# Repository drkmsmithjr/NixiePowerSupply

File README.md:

# [Nixie Tube Power Supply](https://wp.me/p85ddV-B1 )

See [www.surfncircuits.com](https://wp.me/p85ddV-B1)  for a complete description.  This github repository contains the Kicad Schematic, Spice Simulation, Efficiency Calculations of the 5v to 170v DCM Boost Converter for Powering your Nixie Tubes.   

__KC_NixieSupply5vto160v__:  Kicad schematic, PCB layout, BOM.  The footprint is 1.5" x 1.5" and was described and optimized in Part 2 of the blog.     The Board can be ordered from __oshpark.com__.<a href="https://oshpark.com/shared_projects/FZ5eYIVY"></img></a>

__KC_NixieSupply5vto170vMini__:  KiCad schematic, PCB Layout, BOM of the "mini" version of the supply.   This has a footprint of 1.5" x 1" by using smaller output capacitors and using the KiCad power tools to shrink the layout.  This is the system defined by part 3 of the blog.    The layout has all the same constraints as in Part 2.  It still has four mounting holes, a USB input connector and a Terminal output connector.    You can order the board from __oshpark.com__. <a href="https://oshpark.com/shared_projects/UnjheFwg"></img></a>

__SimCalcFiles__:  Spice simulation files and DCM Efficiency Calculations.  NOTE: The LTSPICE (TM) simulation has trouble finding an initial operating point.   To get the simulation to start, use the ESC key and press it twice to skip the initial operating point.   This allows the simulation to continue and will provide a good transient response.    

__Datasheeets__: Datasheets for different inductors and the power fet.  In the Kicad Schematic, the part numbers and Digikey (TM) links are listed already.   Also the complete BOM is located in the KICAD Directory.      

See the complete blogs entry at  www.surfncircuits.com
  * [Designing a Small Footprint, Low Profile 5v to 170v Nixie Tube Power Supply (Part 1)](https://wp.me/p85ddV-A8 )
  * [Optimizing the design of the 5v to 170v Nixie Tube Power Supply (Part 2)](https://wp.me/p85ddV-B1 )
  * [KiCad Power Tools Help Shrink The Nixie Tube Power Supply (part 3)](https://wp.me/p85ddV-Ck)

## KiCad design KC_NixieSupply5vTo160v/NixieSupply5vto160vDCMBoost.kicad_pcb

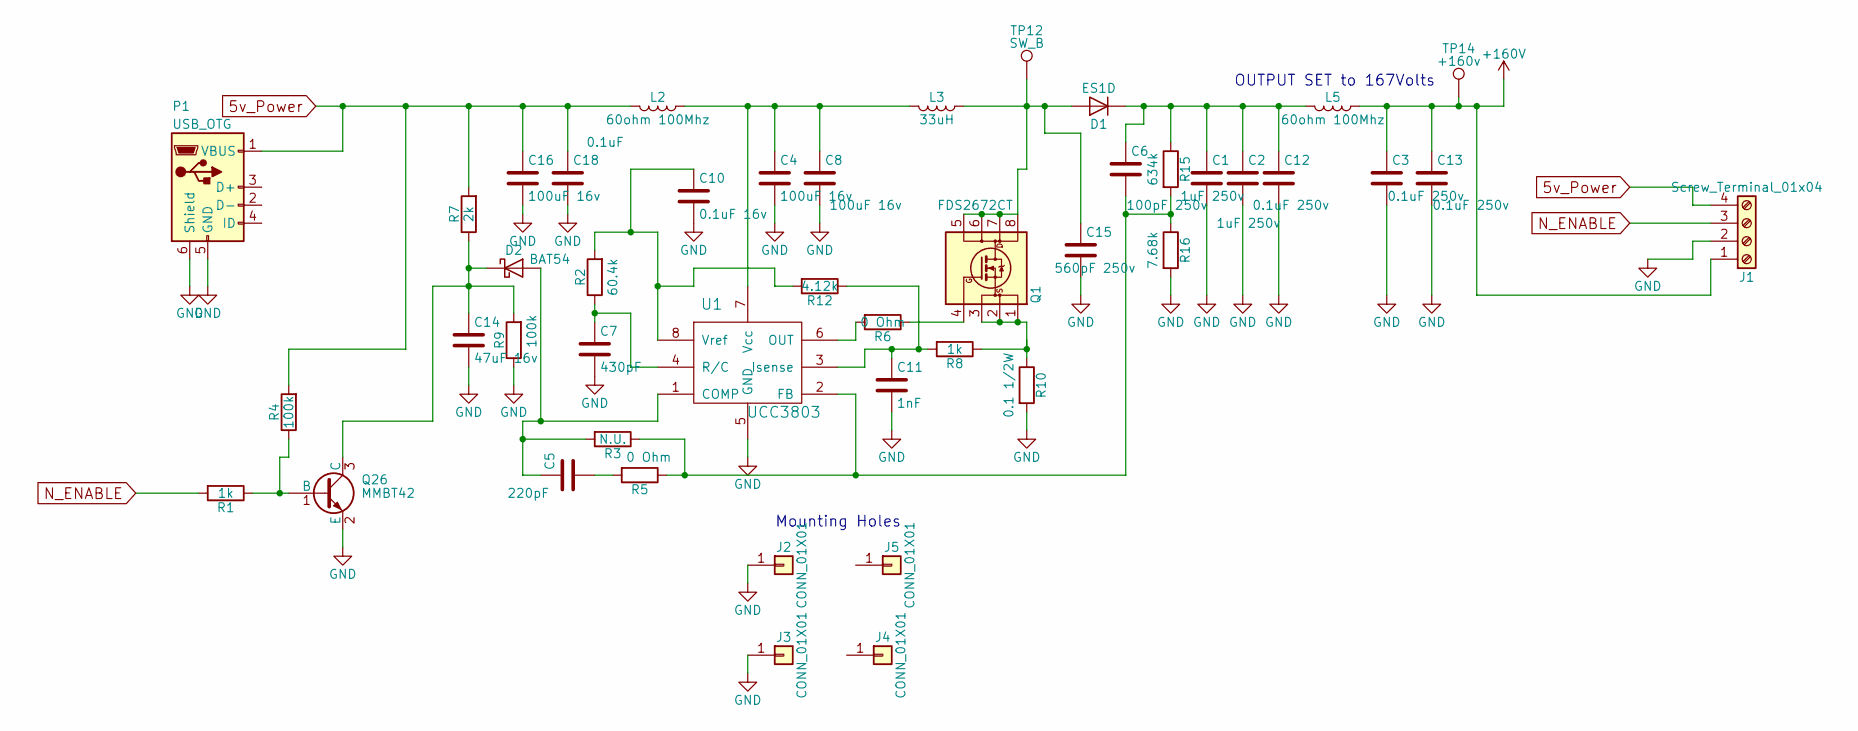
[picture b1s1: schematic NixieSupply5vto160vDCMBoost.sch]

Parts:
C1, C2: 1uF 250v; C_2220_HandSoldering; MPN GRM55DR72E105KW01L
C3, C12, C13: 0.1uF 250v; C_0805; MPN CGA4J3X7T2E104M125AE
C4, C8, C16: 100uF 16v; C_1210; MPN EMK325ABJ107MM-P
C5: 220pF; C_0805
C6: 100pF 250v; C_0805; MPN CC0805C101JAGAC7800
C7: 430pF; C_0805; MPN CL21C431JBANNNC
C10: 0.1uF 16v; C_0805
C11: 1nF; C_0805
C14: 47uF 16v; C_1206; MPN C3216JB1C476M160AB
C15: 560pF 250v; C_0603; MPN C0603C561JAGAC7867
C18: 0.1uF; C_0805
D1: ES1D; D_SMA_Handsoldering; MPN ES1D
D2: BAT54; D_SOD-323_HandSoldering; MPN BAT54WS-7-F
J1: Screw_Terminal_01x04; TerminalBlock_Phoenix_PT-3.5mm_4pol; MPN 1984633
J2, J3: CONN_01X01; MountingHole_2.2mm_M2_Pad
J4, J5: CONN_01X01; MountingHole_2.2mm_M2
L2: 60ohm 100Mhz; R_0805; MPN BKP2125HS600-T
L3: 33uH; Choke_SMD_12x12mm_Wurth_WE-PD; MPN 7447709330
L5: 60ohm 100Mhz; R_0805
P1: USB_OTG; USB_Micro-B_Wurth_3A_Non-OVAL-Drill; MPN 629105150521
Q1: FDS2672CT; SOIC-8-N; MPN FDS2672CT-ND
Q26: MMBT42; SOT-23
R1, R8: 1k; R_0805
R2: 60.4k; R_0805
R3: N.U.; R_0805
R4, R9: 100k; R_0805
R5, R6: 0 Ohm; R_0805
R7: 2k; R_0805
R10: 0.1 1/2W; R_0805; MPN ERJ-6DSFR10V
R12: 4.12k; R_0805
R15: 634k; R_0805
R16: 7.68k; R_0805
TP12: SW_B; PINTST
TP14: +160v; PINTST
U1: UCC3803; SOIC-8-N; MPN UCC3803DTR

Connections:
5v_Power: C16.1, C18.1, J1.4, L2.2, P1.1 (VBUS), R4.2, R7.2
+160V: C3.1, C13.1, J1.1, L5.1, TP14.1
GND: C1.2, C2.2, C3.2, C4.2, C7.2, C8.2, C10.2, C11.2, C12.2, C13.2, C14.2, C15.2, C16.2, C18.2, J1.2, J2.1, J3.1, P1.5 (GND), P1.6 (Shield), Q26.2 (E), R9.1, R10.2, R16.2, U1.5 (GND)
N_ENABLE: J1.3, R1.2
unnamed: C1.1, C2.1, C6.1, C12.1, D1.1 (K), L5.2, R15.1
unnamed: C4.1, C8.1, L2.1, L3.2, U1.7 (Vcc)
unnamed: C5.1, D2.2 (A), R3.2, U1.1 (COMP)
unnamed: C5.2, R5.2
unnamed: C6.2, R3.1, R5.1, R15.2, R16.1, U1.2 (FB)
unnamed: C7.1, R2.1, U1.4 (R/C)
unnamed: C10.1, R2.2, R12.2, U1.8 (Vref)
unnamed: C11.1, R8.2, R12.1, U1.3 (Isense)
unnamed: C14.1, D2.1 (K), Q26.3 (C), R7.1, R9.2
unnamed: C15.1, D1.2 (A), L3.1, Q1.5 (D), Q1.6 (D), Q1.7 (D), Q1.8 (D), TP12.1
unnamed: P1.2 (D-), P1.3 (D+)
unnamed: Q1.1 (S), Q1.2 (S), Q1.3 (S), R8.1, R10.1
unnamed: Q1.4 (G), R6.1
unnamed: Q26.1 (B), R1.1, R4.1
unnamed: R6.2, U1.6 (OUT)

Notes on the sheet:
Mounting Holes
OUTPUT SET to 167Volts

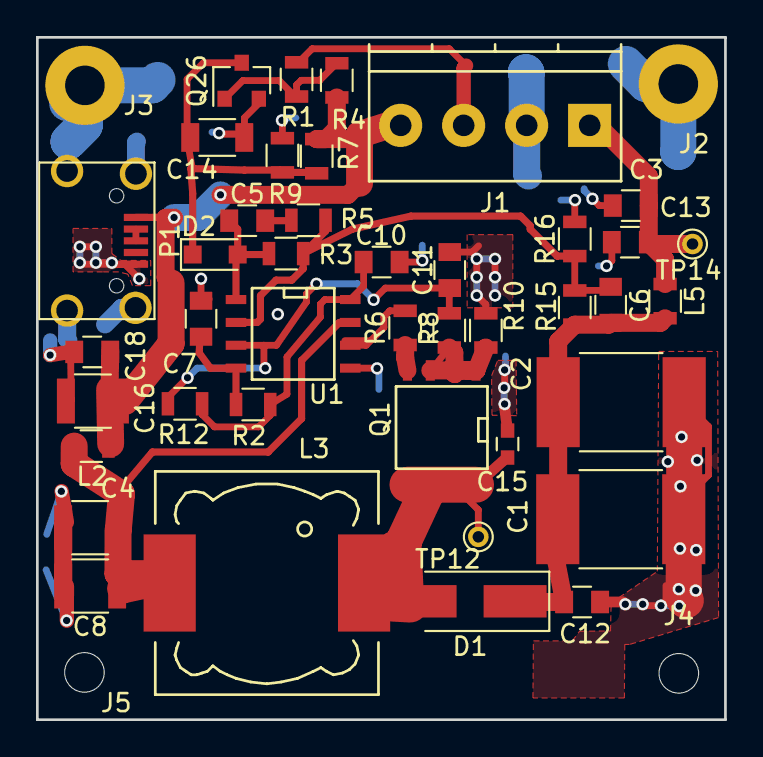
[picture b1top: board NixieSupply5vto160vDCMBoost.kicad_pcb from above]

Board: 2 copper layers, 38.2 x 37.9 mm, 45 parts (0 on the bottom side), 19 nets.

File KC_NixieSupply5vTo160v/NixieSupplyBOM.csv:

,,,,,,
Tool:,Eeschema 4.0.7,,,,,
Generator:,C:/Program Files/KiCad/bin/scripting/plugins/bom_csv_grouped_by_value.py,,,,,
,,,,,,
Item,Qty,Reference(s),Value,Footprint,Datasheet,MPN
1,2,"C1, C2",1uF 250v,Capacitors_SMD:C_2220_HandSoldering,https://www.digikey.com/product-detail/en/murata-electronics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,GRM55DR72E105KW01L
2,3,"C3, C12, C13",0.1uF 250v,Capacitors_SMD:C_0805,,
3,5,"C4, C8, C9, C14, C16",47uF 10v,Capacitors_SMD:C_0805,http://www.digikey.com/product-detail/en/murata-electronics-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,GRM21BR61A476ME15L
4,1,C5,220pF,Capacitors_SMD:C_0805,,
5,1,C6,100pF 250v,Capacitors_SMD:C_0805,,
6,1,C7,330pF,Capacitors_SMD:C_0805,,
7,1,C10,0.1uF 16v,Capacitors_SMD:C_0805,,
8,1,C11,1nF,Capacitors_SMD:C_0805,,
9,1,C15,47pF 250v,Capacitors_SMD:C_0603,http://www.digikey.com/product-detail/en/tdk-corporation/C16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,C1608C0G2E331J080AA
10,1,C18,0.1uF,Capacitors_SMD:C_0805,,
11,1,D1,DFLS1200-7,Diodes_SMD:D_PowerDI-123,https://www.digikey.com/product-detail/en/diodes-incorporate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,DFLS1200-7 
12,1,D2,BAT54,Diodes_SMD:D_SOD-323_HandSoldering,https://www.digikey.com/product-detail/en/diodes-incorporate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,BAT54WS-7-F
13,1,J1,Screw_Terminal_1x04,TerminalBlock_Phoenix:TerminalBlock_Phoenix_PT-3.5mm_4pol,,
14,2,"J2, J3",CONN_01X01,Mounting_Holes:MountingHole_2.2mm_M2_Pad,,
15,2,"J4, J5",CONN_01X01,Mounting_Holes:MountingHole_2.2mm_M2,,
16,2,"L2, L5",60ohm 100Mhz,Resistors_SMD:R_0805,https://www.digikey.com/product-detail/en/taiyo-yuden/BKP212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,BKP2125HS600-T 
17,1,L3,33uH,NixieSupply5vto160vDCMBoost_socket:Choke_SMD_12x12mm_Wurth_WE-PD,https://www.digikey.com/products/en/inductors-coils-chokes/f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,7447709330
18,1,P1,USB_OTG,NixieSupply5vto160vDCMBoost_socket:USB_Micro-B_Wurth_3A,https://www.digikey.com/product-detail/en/wurth-electronics-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,6.29105E+11
19,1,Q1,FDS2734CT,etaclock:SOIC-8-N,https://www.digikey.com/product-detail/en/on-semiconductor/F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,FDS2672CT-ND
20,1,Q26,MMBTA42,TO_SOT_Packages_SMD:SOT-23,http://www.digikey.com/product-detail/en/micro-commercial-co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,
21,2,"R1, R8",1k,Resistors_SMD:R_0805,,
22,1,R2,60.4k,Resistors_SMD:R_0805,,
23,1,R3,N.U.,Resistors_SMD:R_0805,,
24,2,"R4, R9",100k,Resistors_SMD:R_0805,,
25,1,R5,0 Ohm,Resistors_SMD:R_0805,,
26,1,R6,10,Resistors_SMD:R_0805,,
27,1,R7,2k,Resistors_SMD:R_0805,,
28,1,R10,0.1 1/2W,Resistors_SMD:R_0805,https://www.digikey.com/product-detail/en/panasonic-electron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,ERJ-6DSFR10V
29,1,R11,20 0.5W,Resistors_SMD:R_0805,,
30,1,R12,8.2k,Resistors_SMD:R_0805,,
31,1,R15,634k,Resistors_SMD:R_0805,,
32,1,R16,7.68k,Resistors_SMD:R_0805,,
33,1,U1,UCC3803,NixieSupply5vto160vDCMBoost_socket:SOIC-8-N,https://www.digikey.com/products/en/integrated-circuits-ics/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,UCC3803DTR

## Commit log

2018-01-01 :space_invader: Added .gitattributes & .gitignore files
2018-01-01 Initial Upload
    Draft of the blog data files, simulation files. Licence, README
    started but needs to be completed
2018-01-01 change the bom file
2018-01-01 Update .gitignore
    Added Kicad backup files. Don't need these.
2018-01-01 New Gerber Files
    Updated the layout of the USB connector to remove the Slots and replace
    with holes.
2018-01-01 updated layout
    latest. misc
2018-01-01 removed the backup files
    from Kicad
2018-01-01 Update README.md
    UPdated link to the blog
2018-01-06 Update .gitattributes
    changed content to Kicad Layou
2018-01-07 test change
    see if the .gitignore works
2018-01-07 Flyback Efficiency Calculations
    Added a Efficiency calculations for a flyback converter using similar
    parts, but with an off the self 8.5uH 1:5 turns ration flyback
    transformer. the DCM boost still looks like the highest efficiency.
2018-02-01 Latest updates for the verification Blog
2018-02-01 new verification files added during experimental state
2018-02-01 New Gerber's for the final design
2018-02-02 Adding link to the Part 2 of the blog
2018-02-03 NEw BOM with Part 2 of Blog
2018-02-03 removed this 22uH inductor datasheet
2018-02-03 Updated gerber file generation for part 2 of blog
2018-02-04 Update README.md
    Updated readme description and added request for layout help.
2018-02-04 Added the new Mini Layout file to the repository. This is currently a work in progress
2018-02-04 started layout and fixed netclass for the high current 5v input
2018-02-05 Finished the Gerber file for Mini Layout. Need to add OSHW logo to bottom.
2018-02-05 Update README.md
    Added copyright to the PCB board
2018-02-05 Updated the copyright information to Mark Smith and added www.surfncircuits.com to Boards Also added a part number and date code. yyww (last two digits of year and ww is the work week) NixieSupply Re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
2018-02-07 Schematic of the 5v to 170v DCM boost converter
2018-02-07 PNG of the schematic
2018-02-14 Added OSHW_LOGO and the copyright symbol to both Files. Also updated the gerber files and finished the Mini layout solution.
2018-02-14 modified license agreement
2018-02-20 Corrected the C6 BOM entry. Also created a BOM for the MINI version of the layout.
2018-02-20 updated the .gitignore file
2018-02-20 removed backup files
2018-02-20 test update
2018-02-24 restored PCB file I accidentally deleted before.
2018-03-04 Updated the gerber files to include a ground pad for R10 to reduce resistance. Also updated the net classes for the blog entry.
2018-03-04 Updated readme after Part 3 of blog was published
2018-03-04 Update README.md
    Adding Oshpark order code
2018-03-04 Update README.md
    updated the Part 3 link
2018-03-15 New Rev 3 for the Original Nixie Power Supply 1. Corner Mounting Holes are now Solid. Per the tip by comment reader 2. The original supply has a better ground connection for the USB input, But the US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
2018-03-23 Rev 3 of the Mini Nixie Tube Power supply schematic and layout. Changed the output connector to have 1.25mm spacing with nearest conductor
    Moved traces around to allow forn two output connectors. Changed
    the size of the 47uF 16v capacitor to a 1210 package.
2018-03-24 New Gerbers for Rev 3 of the supply. Improved spacing for the 170v output connector. Two output connectors to the correct spacing
2018-03-24 Delete LICENSE~
    removal
2018-03-24 fixed the readme file
2018-03-24 added 3d image of Rev Three to
2018-03-24 updated readme to have the 3D model of the Rev 3 Mini Supply
2021-05-30 This saves Kicad version 4.0 o of the nixie power supplies.
2021-07-16 The NewOrigin Zip file was used for the PCBWAY order This BOM was used for the PCBway order Updated the files to Rev 5 of Kicad
2021-07-16 Files for the pcbway order
2021-07-16 added all files
2021-12-20 version Kicad version 5. 170vmini supply is up to date with 3D images.
